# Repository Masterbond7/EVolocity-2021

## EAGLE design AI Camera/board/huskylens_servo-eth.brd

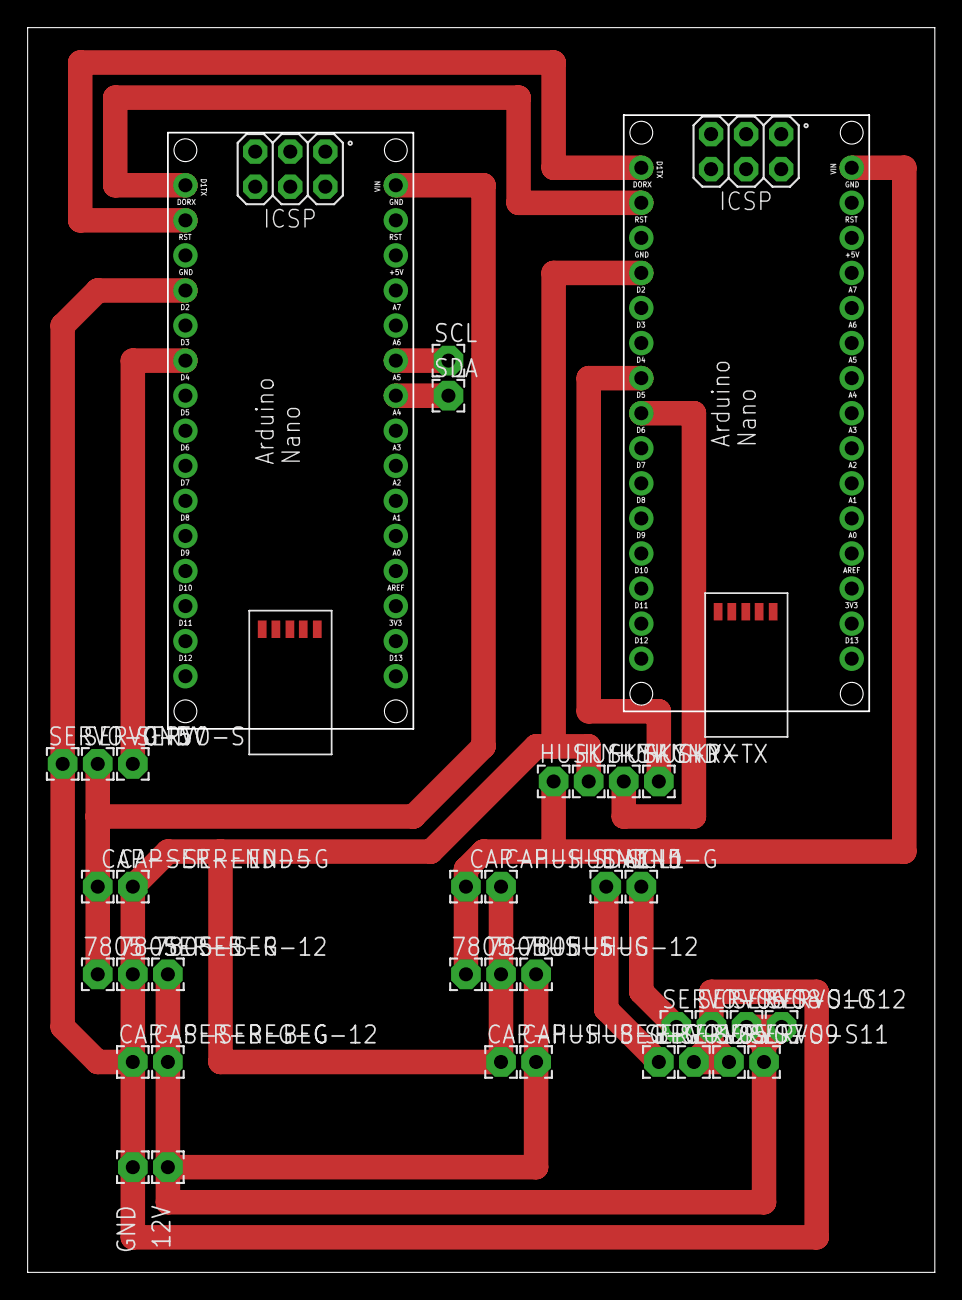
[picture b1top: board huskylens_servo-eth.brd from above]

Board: 2 copper layers, 65.7 x 90.2 mm, 37 parts (0 on the bottom side), 13 nets.

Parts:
12V, 7805-HUS-5, 7805-HUS-12, 7805-HUS-G, 7805-SER-5, 7805-SER-12, 7805-SER-G: 2,15/1,0
CAP-HUS-BEG-12: 2,15/1,0
CAP-HUS-BEG-G: 2,15/1,0
CAP-HUS-END-5: 2,15/1,0
CAP-HUS-END-G: 2,15/1,0
CAP-SER-BEG-12: 2,15/1,0
CAP-SER-BEG-G: 2,15/1,0
CAP-SER-END-5: 2,15/1,0
CAP-SER-END-G: 2,15/1,0
GND: 2,15/1,0
HUSKY-5V: 2,15/1,0
HUSKY-ARD: ARDUINO_NANO
HUSKY-GND: 2,15/1,0
HUSKY-RX: 2,15/1,0
HUSKY-TX: 2,15/1,0
SCL, SCL1: 2,15/1,0
SDA, SDA1: 2,15/1,0
SERVO-5V: 2,15/1,0
SERVO-ARD: ARDUINO_NANO
SERVO-GND: 2,15/1,0
SERVO-S, SERVO-S5, SERVO-S6, SERVO-S7, SERVO-S8, SERVO-S9, SERVO-S10, SERVO-S11, SERVO-S12: 2,15/1,0

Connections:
unnamed: HUSKY-ARD.RX1, SERVO-ARD.TX1
unnamed: HUSKY-ARD.TX1, SERVO-ARD.RX1
unnamed: 7805-HUS-G.1, 7805-SER-G.1, CAP-HUS-BEG-G.1, CAP-HUS-END-G.1, CAP-SER-BEG-G.1, CAP-SER-END-G.1, GND.1, HUSKY-ARD.GND, HUSKY-GND.1, SERVO-ARD.GND, SERVO-GND.1, SERVO-S7.1, SERVO-S8.1, SERVO-S9.1
unnamed: HUSKY-ARD.D5, HUSKY-RX.1
unnamed: SERVO-ARD.D3, SERVO-S.1
unnamed: 12V.1, 7805-HUS-12.1, 7805-SER-12.1, CAP-HUS-BEG-12.1, CAP-SER-BEG-12.1, SERVO-S10.1, SERVO-S11.1, SERVO-S12.1
unnamed: 7805-HUS-5.1, CAP-HUS-END-5.1, HUSKY-5V.1, HUSKY-ARD.VIN
unnamed: 7805-SER-5.1, CAP-SER-END-5.1, SERVO-5V.1, SERVO-ARD.VIN
unnamed: HUSKY-ARD.D4, HUSKY-TX.1
S$1: SCL.1, SERVO-ARD.A6
S$2: SDA.1, SERVO-ARD.A5
S$3: SDA1.1, SERVO-S5.1
S$4: SCL1.1, SERVO-S6.1

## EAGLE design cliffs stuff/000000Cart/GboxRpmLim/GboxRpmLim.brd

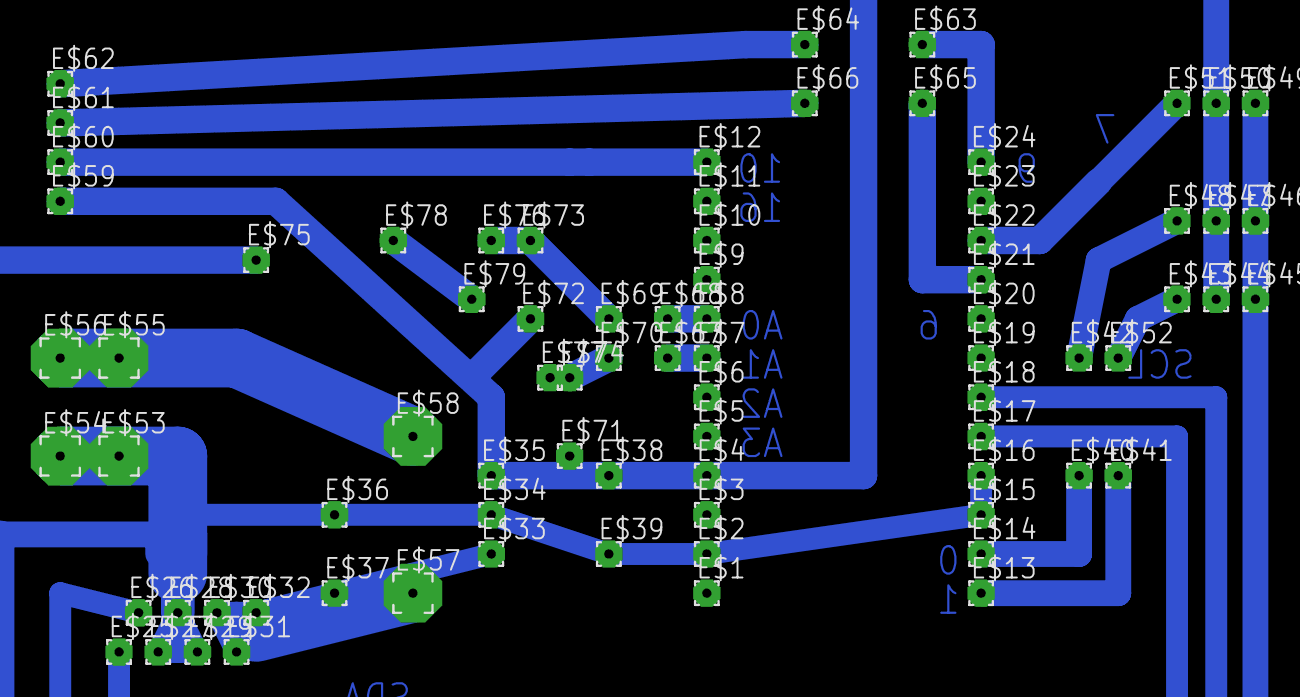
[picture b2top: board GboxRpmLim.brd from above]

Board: 2 copper layers, 79 parts (0 on the bottom side), 20 nets.

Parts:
E$1, E$2, E$3, E$4, E$5, E$6, E$7, E$8, E$9, E$10, E$11, E$12, E$13, E$14, E$15, E$16, E$17, E$18, E$19, E$20, E$21, E$22, E$23, E$24, E$25, E$26, E$27, E$28, E$29, E$30, E$31, E$32, E$33, E$34, E$35, E$36, E$37, E$38, E$39, E$40, E$41, E$42, E$43, E$44, E$45, E$46, E$47, E$48, E$49, E$50, E$51, E$52, E$59, E$60, E$61, E$62, E$63, E$64, E$65, E$66, E$67, E$68, E$69, E$70, E$71, E$72, E$73, E$74, E$75, E$76, E$77, E$78, E$79: 1,6/0,8
E$53, E$54, E$55, E$56, E$57, E$58: 2,54/0,8

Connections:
S$1: E$61.1, E$66.1
S$2: E$30.1, E$31.1, E$32.1, E$33.1, E$37.1
S$3: E$17.1, E$25.1
S$4: E$18.1, E$26.1
S$5: E$35.1, E$38.1, E$44.1, E$47.1, E$50.1, E$59.1
S$6: E$45.1, E$46.1, E$49.1
S$7: E$8.1, E$68.1
S$8: E$14.1, E$40.1
S$9: E$13.1, E$41.1
S$10: E$42.1, E$48.1
S$11: E$43.1, E$52.1
S$12: E$2.1, E$15.1, E$16.1, E$27.1, E$28.1, E$29.1, E$34.1, E$36.1, E$39.1, E$54.1
S$14: E$56.1, E$58.1
S$17: E$62.1, E$64.1
S$18: E$22.1, E$51.1
S$20: E$12.1, E$60.1
S$21: E$7.1, E$67.1
S$22: E$70.1, E$74.1
S$23: E$69.1, E$73.1, E$76.1
S$25: E$78.1, E$79.1

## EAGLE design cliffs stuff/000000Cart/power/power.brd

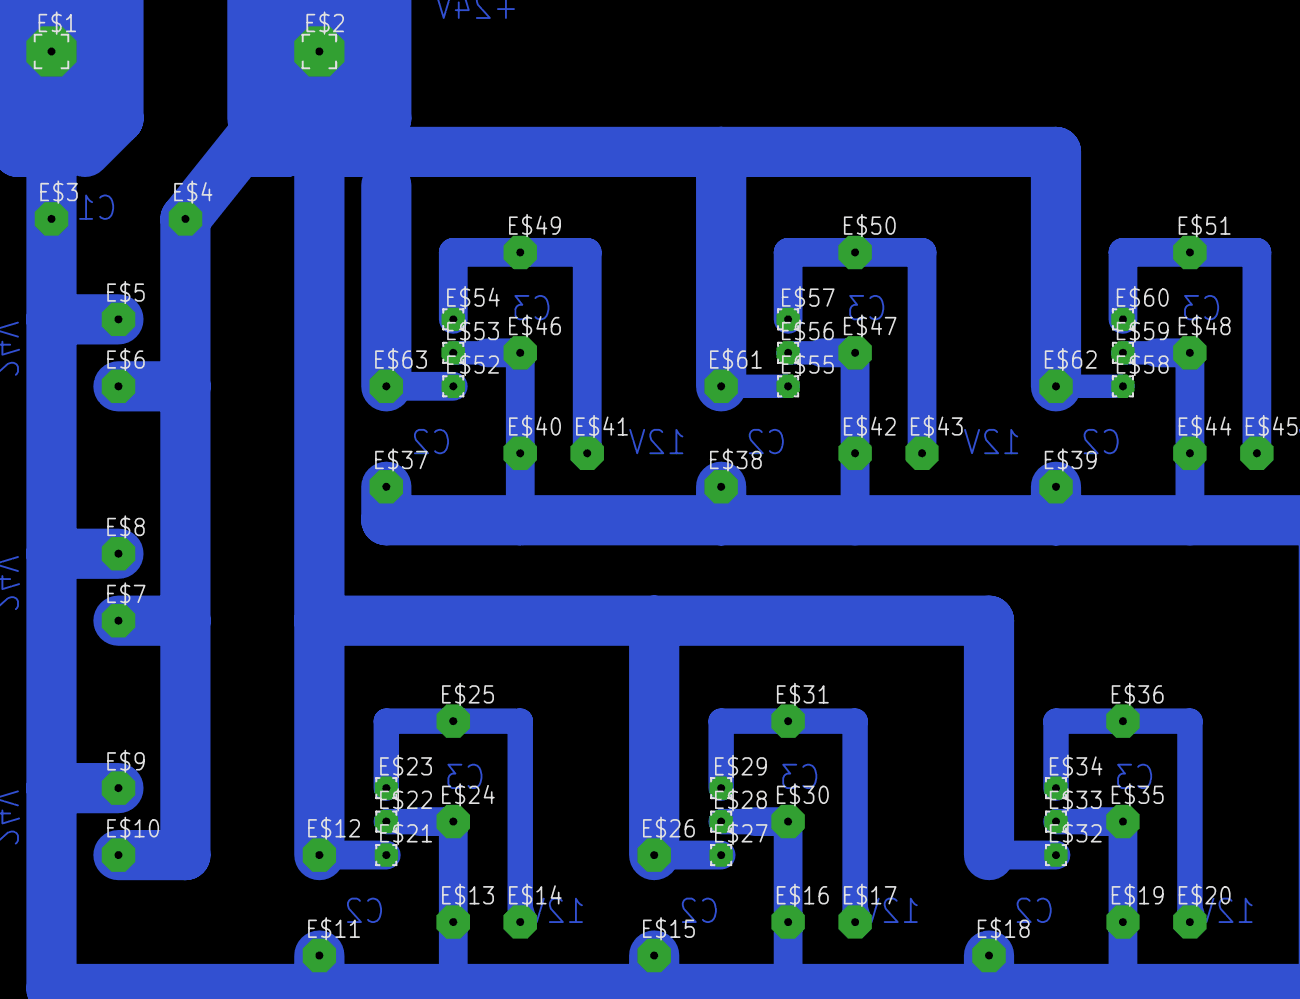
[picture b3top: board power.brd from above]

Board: 2 copper layers, 63 parts (0 on the bottom side), 8 nets.

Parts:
E$1, E$2: 2,54/0,8
E$3, E$4, E$5, E$6, E$7, E$8, E$9, E$10, E$11, E$12, E$13, E$14, E$15, E$16, E$17, E$18, E$19, E$20, E$24, E$25, E$26, E$30, E$31, E$35, E$36, E$37, E$38, E$39, E$40, E$41, E$42, E$43, E$44, E$45, E$46, E$47, E$48, E$49, E$50, E$51, E$61, E$62, E$63: 2,15/1,0
E$21, E$22, E$23, E$27, E$28, E$29, E$32, E$33, E$34, E$52, E$53, E$54, E$55, E$56, E$57, E$58, E$59, E$60: 1,6/0,8

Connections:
S$4: E$14.1, E$23.1
S$7: E$17.1, E$29.1
S$9: E$20.1, E$34.1
S$10: E$41.1, E$49.1, E$54.1
S$11: E$2.1, E$4.1, E$6.1, E$7.1, E$10.1, E$12.1, E$21.1, E$26.1, E$27.1, E$52.1, E$55.1, E$58.1, E$63.1
S$13: E$1.1, E$3.1, E$5.1, E$8.1, E$9.1, E$11.1, E$13.1, E$15.1, E$18.1, E$19.1, E$22.1, E$28.1, E$33.1, E$37.1, E$38.1, E$39.1, E$40.1, E$42.1, E$44.1, E$46.1, E$47.1, E$48.1, E$53.1, E$56.1, E$59.1
S$14: E$43.1, E$50.1, E$57.1
S$15: E$45.1, E$51.1, E$60.1
